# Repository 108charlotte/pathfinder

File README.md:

# pathfinder
An unfinished PCB for Hack Club's [https://pathfinder.hackclub.com/](pathfinder) event

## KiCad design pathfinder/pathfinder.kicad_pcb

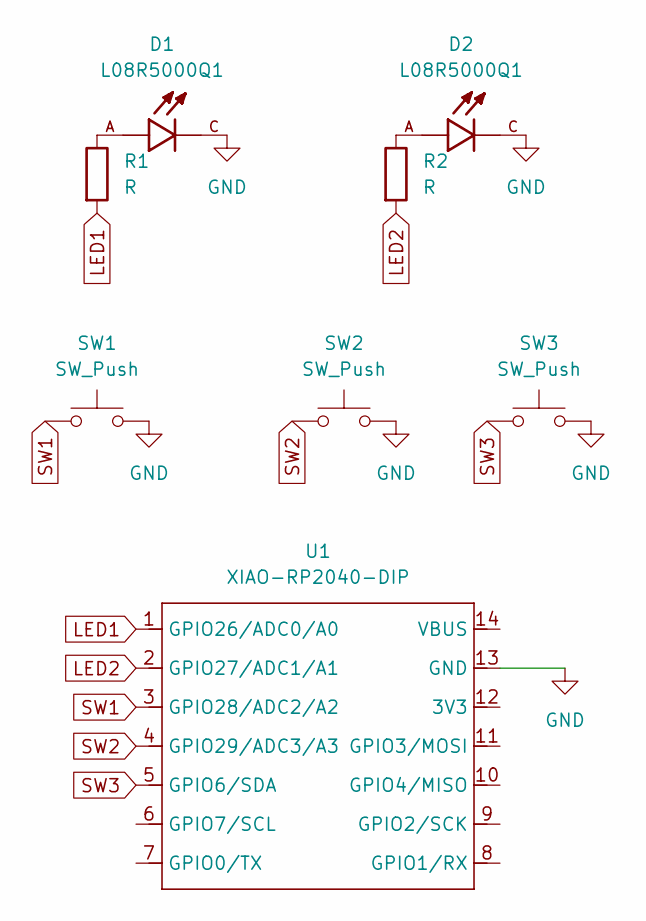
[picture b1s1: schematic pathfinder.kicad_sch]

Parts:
D1, D2: L08R5000Q1; LEDRD254W57D500H1070; PARTREV NA
R1, R2: R; R_Axial_DIN0204_L3.6mm_D1.6mm_P5.08mm_Horizontal
SW1, SW2, SW3: SW_Push; SW_Cherry_MX_1.00u_PCB
U1: XIAO-RP2040-DIP

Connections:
GND: D1.C, D2.C, SW1.2, SW2.2, SW3.2, U1.13 (GND)
LED1: R1.2, U1.1 (GPIO26/ADC0/A0)
LED2: R2.2, U1.2 (GPIO27/ADC1/A1)
unnamed: D1.A, R1.1
unnamed: D2.A, R2.1
SW1: SW1.1, U1.3 (GPIO28/ADC2/A2)
SW2: SW2.1, U1.4 (GPIO29/ADC3/A3)
SW3: SW3.1, U1.5 (GPIO6/SDA)

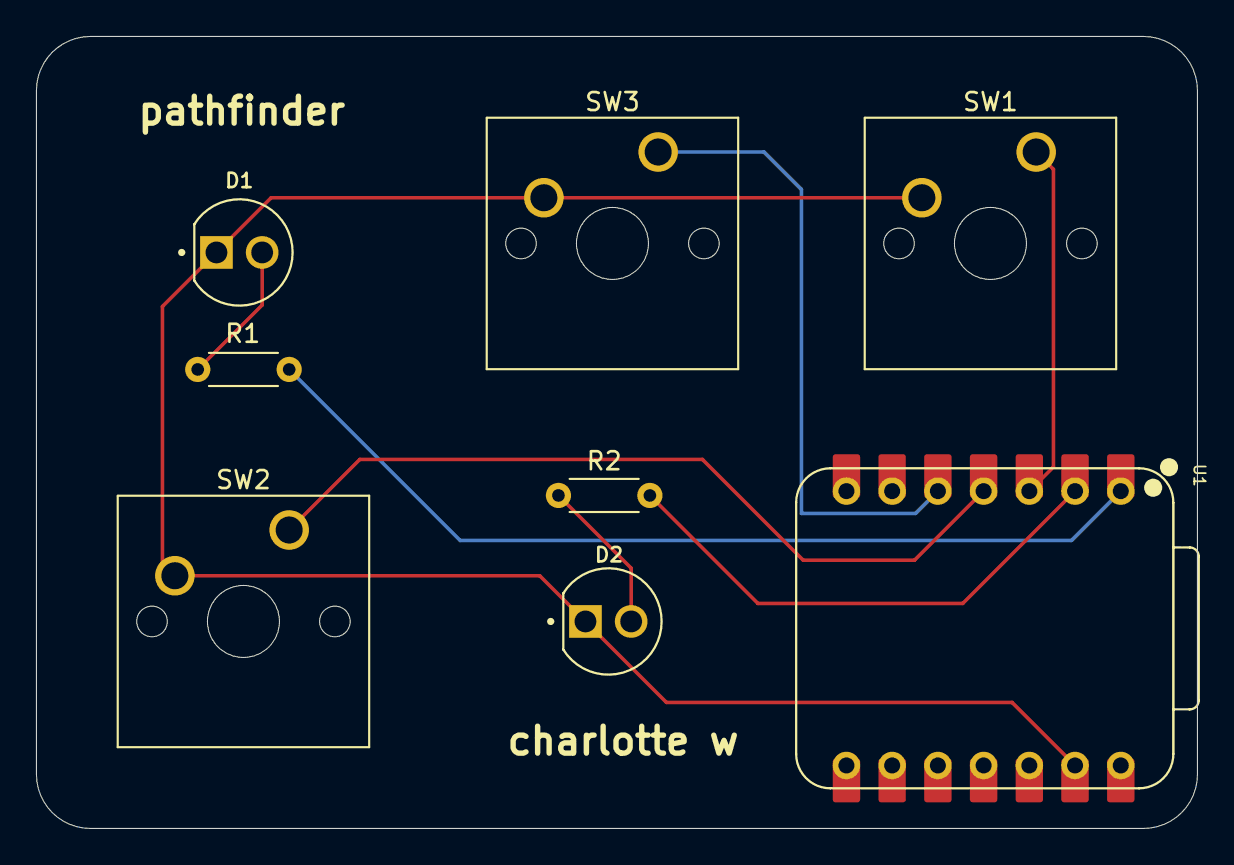
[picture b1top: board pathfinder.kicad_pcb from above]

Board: 2 copper layers, 64.5 x 44.0 mm, 8 parts (0 on the bottom side), 8 nets.

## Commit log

2025-07-01 adding all pcb progress
2026-01-01 added simple description
